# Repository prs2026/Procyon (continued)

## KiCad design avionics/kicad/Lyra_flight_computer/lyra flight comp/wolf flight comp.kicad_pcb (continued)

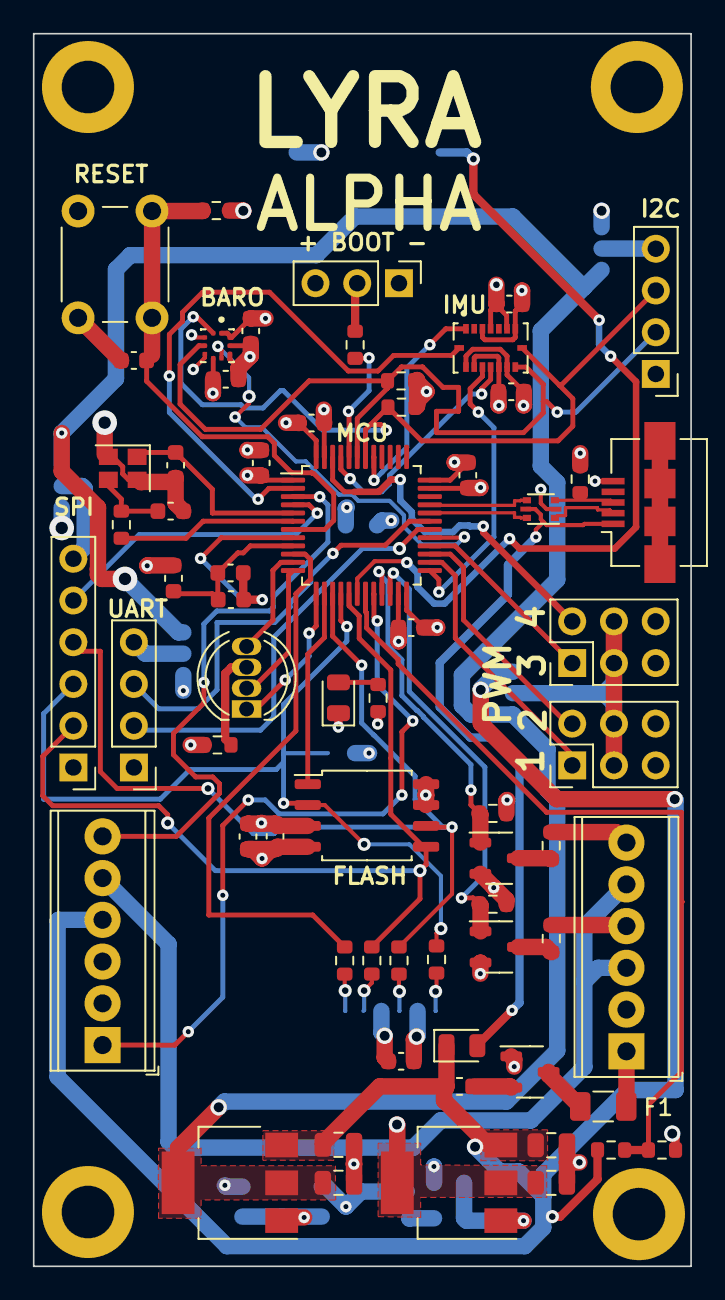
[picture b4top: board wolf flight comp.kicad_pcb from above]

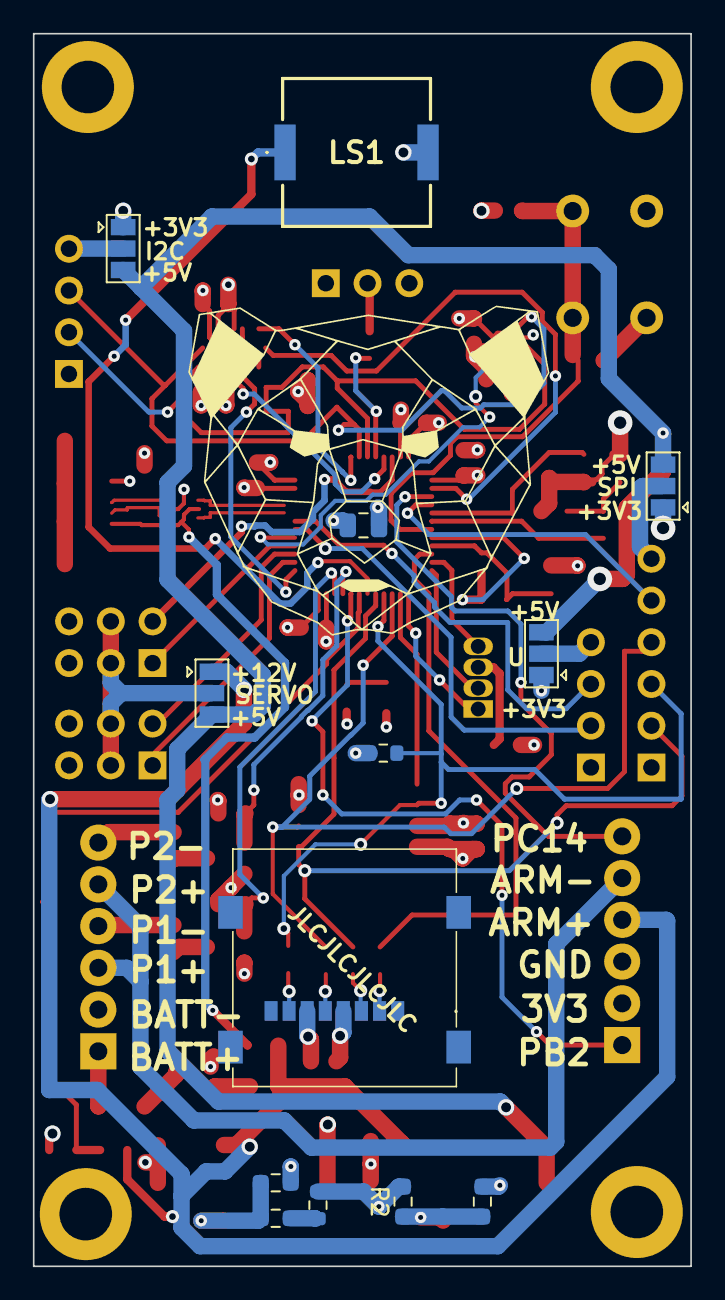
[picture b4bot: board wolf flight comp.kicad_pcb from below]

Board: 4 copper layers, 40.0 x 75.0 mm, 82 parts (13 on the bottom side), 65 nets.

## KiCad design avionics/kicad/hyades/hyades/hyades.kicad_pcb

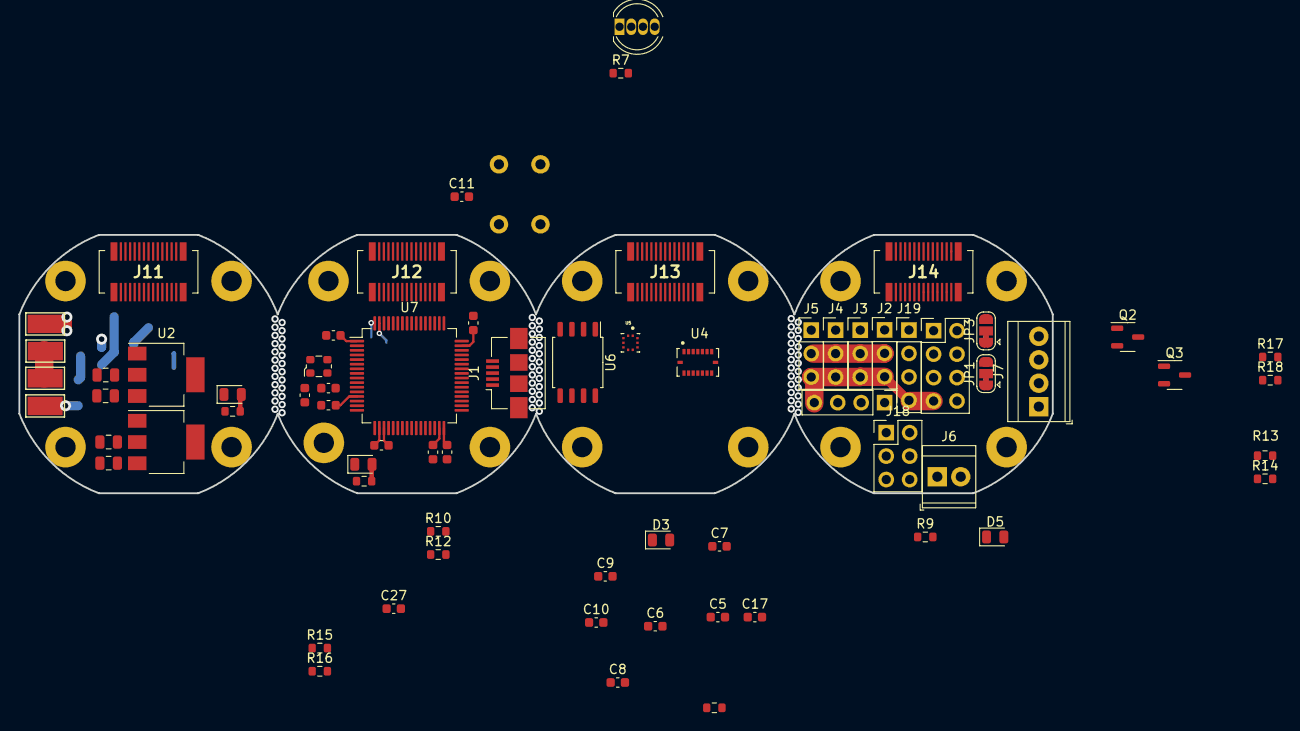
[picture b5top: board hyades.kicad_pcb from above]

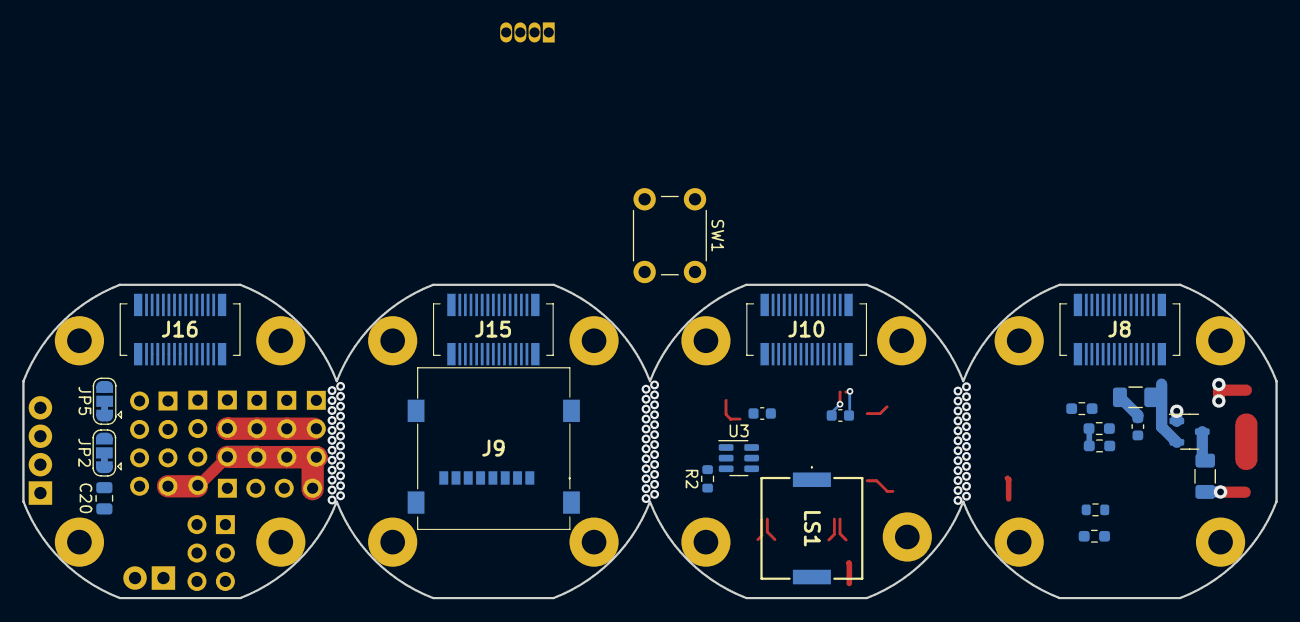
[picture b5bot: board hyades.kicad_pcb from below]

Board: 4 copper layers, 112.0 x 28.0 mm, 108 parts (23 on the bottom side), 64 nets.

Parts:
C1, C2: 0.1uf; C_0805_2012Metric
C3, C4: 1uf; C_0805_2012Metric
C5, C6, C7, C8, C10, C19: 0.1uf; C_0603_1608Metric
C9, C17, C18: 1uf; C_0603_1608Metric
C11, C12, C13, C14, C15, C16, C27: 100nf; C_0603_1608Metric
C20: 100uf; C_0805_2012Metric
C28, C29: 2u2; C_0603_1608Metric
D2: LED_GKRB; LED_D5.0mm-4_RGB
D3, D4, D5, D6: LED; LED_0805_2012Metric
F1: 2a; Fuse_1206_3216Metric
F2: 200ma; Fuse_1206_3216Metric
FB1: 600 @600mhz; L_0603_1608Metric
FB2: 600 @ 600MHz; L_0603_1608Metric
H1, H2, H3, H4, H5, H6, H7, H8, H9, H10, H11, H12, H13, H14, H15, H16: MountingHole_Pad; MountingHole_2.2mm_M2_Pad
J1: USB_B_Micro; USB_Micro-B_Amphenol_10104110_Horizontal
J2: Servo1; PinHeader_1x03_P2.54mm_Vertical
J3: Servo2; PinHeader_1x03_P2.54mm_Vertical
J4: Servo3; PinHeader_1x03_P2.54mm_Vertical
J5: Servo4; PinHeader_1x03_P2.54mm_Vertical
J6: Screw_Terminal_01x02; TerminalBlock_TE_282834-2_1x02_P2.54mm_Horizontal
J7: Screw_Terminal_01x04; TerminalBlock_TE_282834-4_1x04_P2.54mm_Horizontal
J8, J10, J15, J16: BOARDTOBOARDB; AXK5S30347YG
J9: MEM2067-02-180-00-A; MEM20670218000A
J11, J12, J13, J14: BOARDTOBOARDF; AXK5S30347YG
J17: Conn_02x04_Odd_Even; PinHeader_2x04_P2.54mm_Vertical
J18: SPI HEADER; PinHeader_2x03_P2.54mm_Vertical
J19: I2C HEADER; PinHeader_1x04_P2.54mm_Vertical
J20: UART HEADER; PinHeader_1x04_P2.54mm_Vertical
JP1: Servo Power; SolderJumper-3_P1.3mm_Bridged12_RoundedPad1.0x1.5mm
JP2: I2C POWER; SolderJumper-3_P1.3mm_Bridged12_RoundedPad1.0x1.5mm
JP3: UART POWER; SolderJumper-3_P1.3mm_Bridged12_RoundedPad1.0x1.5mm
JP5: SPI Power; SolderJumper-3_P1.3mm_Bridged12_RoundedPad1.0x1.5mm
LS1: PKMCS0909E4000-R1; PKMCS0909E4000R1
Q1: AO3401A; SOT-23-3
Q2, Q3: Q_NMOS_GSD; SOT-23-3
R1: 400; R_0603_1608Metric
R2: 1k5; R_0603_1608Metric
R3: 400; R_0603_1608Metric_Pad0.98x0.95mm_HandSolder
R4: 330; R_0603_1608Metric_Pad0.98x0.95mm_HandSolder
R5, R6: 240; R_0603_1608Metric_Pad0.98x0.95mm_HandSolder
R7, R8, R9, R11, R13, R17, R19: 470; R_0603_1608Metric
R10: 20k; R_0603_1608Metric
R12: 6k; R_0603_1608Metric
R14, R18: 10; R_0603_1608Metric
R15, R16: 2k2; R_0603_1608Metric
SW1: SW_MEC_5E; SW_PUSH_6mm
TP1, TP2, TP3, TP4: Connector; TestPoint_Keystone_5019_Minature
U1, U2: LM317_SOT-223; SOT-223-3_TabPin2
U3: USBLC6-2SC6; SOT-23-6
U4: BMI088; PQFN50P450X300X100-16N
U5: BMP390L; XDCR_BMP390L
U6: W25Q32JVSS; SOIC-8_5.23x5.23mm_P1.27mm
U7: STM32F405RGTx; LQFP-64_10x10mm_P0.5mm
X1: ECS-2520MV-xxx-xx; Oscillator_SMD_ECS_2520MV-xxx-xx-4Pin_2.5x2.0mm

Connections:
+3.3VA: C18.2, C19.2, FB2.1, U7.13 (VDDA), X1.1 (Tri-State), X1.4 (VDD)
+3V3: C3.1, C5.1, C6.1, C7.1, C8.1, C9.2, C10.2, C12.2, C13.2, C14.2, C15.2, C16.2, C17.2, C27.2, FB2.2, J8.1, J9.P4 (VDD), J10.1, J11.2, J12.2, J13.2, J14.2, J15.1, J16.1, J17.6, J17.8, JP2.1 (A), JP3.1 (A), JP5.1 (A), R2.1, R5.1, R8.2, R9.2, R11.2, R15.1, R16.1, R19.2, U1.2 (VO), U4.3 (VDD), U4.7 (PS), U4.11 (VDDIO), U4.14 (CSB1), U5.1 (VDDIO), U5.6 (~CS), U5.10 (VDD), U6.3 (IO2), U6.7 (IO3), U6.8 (VCC), U7.1 (VBAT), U7.19 (VDD), U7.32 (VDD), U7.48 (VDD), U7.64 (VDD)
+5V: C4.1, J8.4, J8.6, J10.4, J10.6, J11.3, J11.5, J12.3, J12.5, J13.3, J13.5, J14.3, J14.5, J15.4, J15.6, J16.4, J16.6, JP1.1 (A), JP2.3 (B), JP3.3 (B), JP5.3 (B), R6.1, U2.2 (VO)
+12P: F2.1, J6.1, J8.8, J8.10, J10.8, J10.10, J11.7, J11.9, J12.7, J12.9, J13.7, J13.9, J14.7, J14.9, J15.8, J15.10, J16.8, J16.10, J17.3, JP1.3 (B), Q1.2 (S), R10.1
+12V: C1.1, C2.1, FB1.2, U1.3 (VI), U2.3 (VI)
+BATT: TP1.1, TP3.1
ACCEL INT1: J8.18, J10.18, J11.17, J12.17, J13.17, J14.17, J15.18, J16.18, U4.16 (INT1), U7.28 (PB2)
ACCEL INT2: J8.16, J10.16, J11.15, J12.15, J13.15, J14.15, J15.16, J16.16, U4.1 (INT2), U7.27 (PB1)
ARM+: J6.2, J7.1, J7.3
BARO INT: J8.24, J10.24, J11.23, J12.23, J13.23, J14.23, J15.24, J16.24, U5.7 (INT/DNC), U7.57 (PB5)
BATT SENSE: R10.2, R12.1, U7.15 (PA1)
BUZZER: LS1.1 (+), U7.58 (PB6)
CS SD: J8.14, J9.P2 (CD/DAT3), J10.14, J11.13, J12.13, J13.13, J14.13, J15.14, J16.14, U7.25 (PC5)
FLASH CS: J8.12, J10.12, J11.11, J12.11, J13.11, J14.11, J15.12, J16.12, U6.1 (~CS), U7.24 (PC4)
GND: C1.2, C2.2, C3.2, C4.2, C5.2, C6.2, C7.2, C8.2, C9.1, C10.1, C11.1, C12.1, C13.1, C14.1, C15.1, C16.1, C17.1, C18.1, C19.1, C20.1, C27.1, C28.2, C29.2, D3.1 (K), D4.1 (K), D5.1 (K), D6.1 (K), H1.1, H2.1, H3.1, H4.1, H5.1, H6.1, H7.1, H8.1, H9.1, H10.1, H11.1, H12.1, H13.1, H14.1, H15.1, H16.1, J1.5 (GND), J2.3, J3.3, J4.3, J5.3, J8.29, J8.30, J9.P6 (VSS), J10.29, J10.30, J11.29, J11.30, J12.29, J12.30, J13.29, J13.30, J14.29, J14.30, J15.29, J15.30, J16.29, J16.30, J17.5, J17.7, J18.3, J19.4, J20.4, LS1.2 (-), Q1.1 (G), Q2.2 (S), Q3.2 (S), R1.2, R4.2, R7.1, R12.2, R13.1, R17.1, SW1.1, TP2.1, U3.2 (GND), U4.4 (GNDA), U4.6 (GNDIO), U4.10 (SDO2), U4.15 (SDO1), U5.3 (VSS/GND), U5.5 (SDO/DNC/SA0), U5.8 (VSS/GND__1), U5.9 (VSS/GND__2), U6.4 (GND), U7.12 (VSSA), U7.18 (VSS), U7.63 (VSS), X1.2 (GND)
GYRO INT3: J8.20, J10.20, J11.19, J12.19, J13.19, J14.19, J15.20, J16.20, U4.12 (INT3), U7.55 (PB3)
GYRO INT4: J8.22, J10.22, J11.21, J12.21, J13.21, J14.21, J15.22, J16.22, U4.13 (INT4), U7.56 (PB4)
I2C POWER: J19.1, JP2.2 (C)
LED BLUE: D2.4 (BA), U7.59 (PB7)
LED GREEN: D2.1 (GA), U7.61 (PB8)
LED RED: D2.3 (RA), U7.62 (PB9)
MISO: J8.23, J9.P7 (DAT0), J10.23, J11.24, J12.24, J13.24, J14.24, J15.23, J16.23, J18.5, U6.2 (DO(IO1)), U7.22 (PA6)
MOSI: J8.25, J9.P3 (CMD), J10.25, J11.26, J12.26, J13.26, J14.26, J15.25, J16.25, J18.6, U6.5 (DI(IO0)), U7.23 (PA7)
unnamed: D2.2 (K), R7.2
unnamed: D3.2 (A), R11.1
unnamed: D4.2 (A), R8.1
unnamed: D5.2 (A), R9.1
unnamed: D6.2 (A), R19.1
unnamed: F2.2, FB1.1
unnamed: F1.2, Q1.3 (D)
unnamed: Q2.3 (D), R14.2
unnamed: Q3.3 (D), R18.2
unnamed: R3.2, R4.1
unnamed: R1.1, R5.2, U1.1 (ADJ)
unnamed: R3.1, R6.2, U2.1 (ADJ)
unnamed: C29.1, U7.31 (VCAP_1)
unnamed: C28.1, U7.47 (VCAP_2)
OSCIN: U7.5 (PH0), X1.3 (OUT)
P1 EN: J8.26, J10.26, J11.25, J12.25, J13.25, J14.25, J15.26, J16.26, Q3.1 (G), R17.2, U7.33 (PB12)
P1-: J7.2, R18.1
P2 EN: J8.28, J10.28, J11.27, J12.27, J13.27, J14.27, J15.28, J16.28, Q2.1 (G), R13.2, U7.34 (PB13)
P2-: J7.4, R14.1
PB14: J8.27, J10.27, J11.28, J12.28, J13.28, J14.28, J15.27, J16.27, J17.1, U7.35 (PB14)
PB15: J8.7, J10.7, J11.8, J12.8, J13.8, J14.8, J15.7, J16.7, J17.2, U7.36 (PB15)
PC8: J8.2, J10.2, J11.1, J12.1, J13.1, J14.1, J15.2, J16.2, J18.2, U7.39 (PC8)
RESET: C11.2, SW1.2, U7.7 (NRST)
SCK: J8.21, J9.P5 (CLK), J10.21, J11.22, J12.22, J13.22, J14.22, J15.21, J16.21, J18.4, U6.6 (CLK), U7.21 (PA5)
SCL: J8.11, J10.11, J11.12, J12.12, J13.12, J14.12, J15.11, J16.11, J19.3, R15.2, U4.8 (SCL/SCK), U5.2 (SCK/SCL), U7.29 (PB10)
SDA: J8.9, J10.9, J11.10, J12.10, J13.10, J14.10, J15.9, J16.9, J19.2, R16.2, U4.9 (SDA/SDI), U5.4 (SDI/SDO/SDA), U7.30 (PB11)
SERVO1: J2.1, J8.13, J10.13, J11.14, J12.14, J13.14, J14.14, J15.13, J16.13, U7.37 (PC6)
SERVO2: J3.1, J8.15, J10.15, J11.16, J12.16, J13.16, J14.16, J15.15, J16.15, U7.38 (PC7)
SERVO3: J4.1, J8.17, J10.17, J11.18, J12.18, J13.18, J14.18, J15.17, J16.17, U7.40 (PC9)
SERVO4: J5.1, J8.19, J10.19, J11.20, J12.20, J13.20, J14.20, J15.19, J16.19, U7.26 (PB0)
SERVOPOWER: C20.2, J2.2, J3.2, J4.2, J5.2, JP1.2 (C)
SPI POWER: J18.1, JP5.2 (C)
TOGGLED12V: F1.1, TP4.1
UART POWER: J20.1, JP3.2 (C)
USART2 RX: J8.5, J10.5, J11.6, J12.6, J13.6, J14.6, J15.5, J16.5, J20.3, U7.17 (PA3)
USART2 TX: J8.3, J10.3, J11.4, J12.4, J13.4, J14.4, J15.3, J16.3, J20.2, U7.16 (PA2)
USB CON D+: J1.3 (D+), R2.2, U3.3 (I/O2)
USB CON D-: J1.2 (D-), U3.1 (I/O1)
USB D+: U3.4 (I/O2), U7.45 (PA12)
USB D-: U3.6 (I/O1), U7.44 (PA11)
VBUS: J1.1 (VBUS), U3.5 (VBUS)
